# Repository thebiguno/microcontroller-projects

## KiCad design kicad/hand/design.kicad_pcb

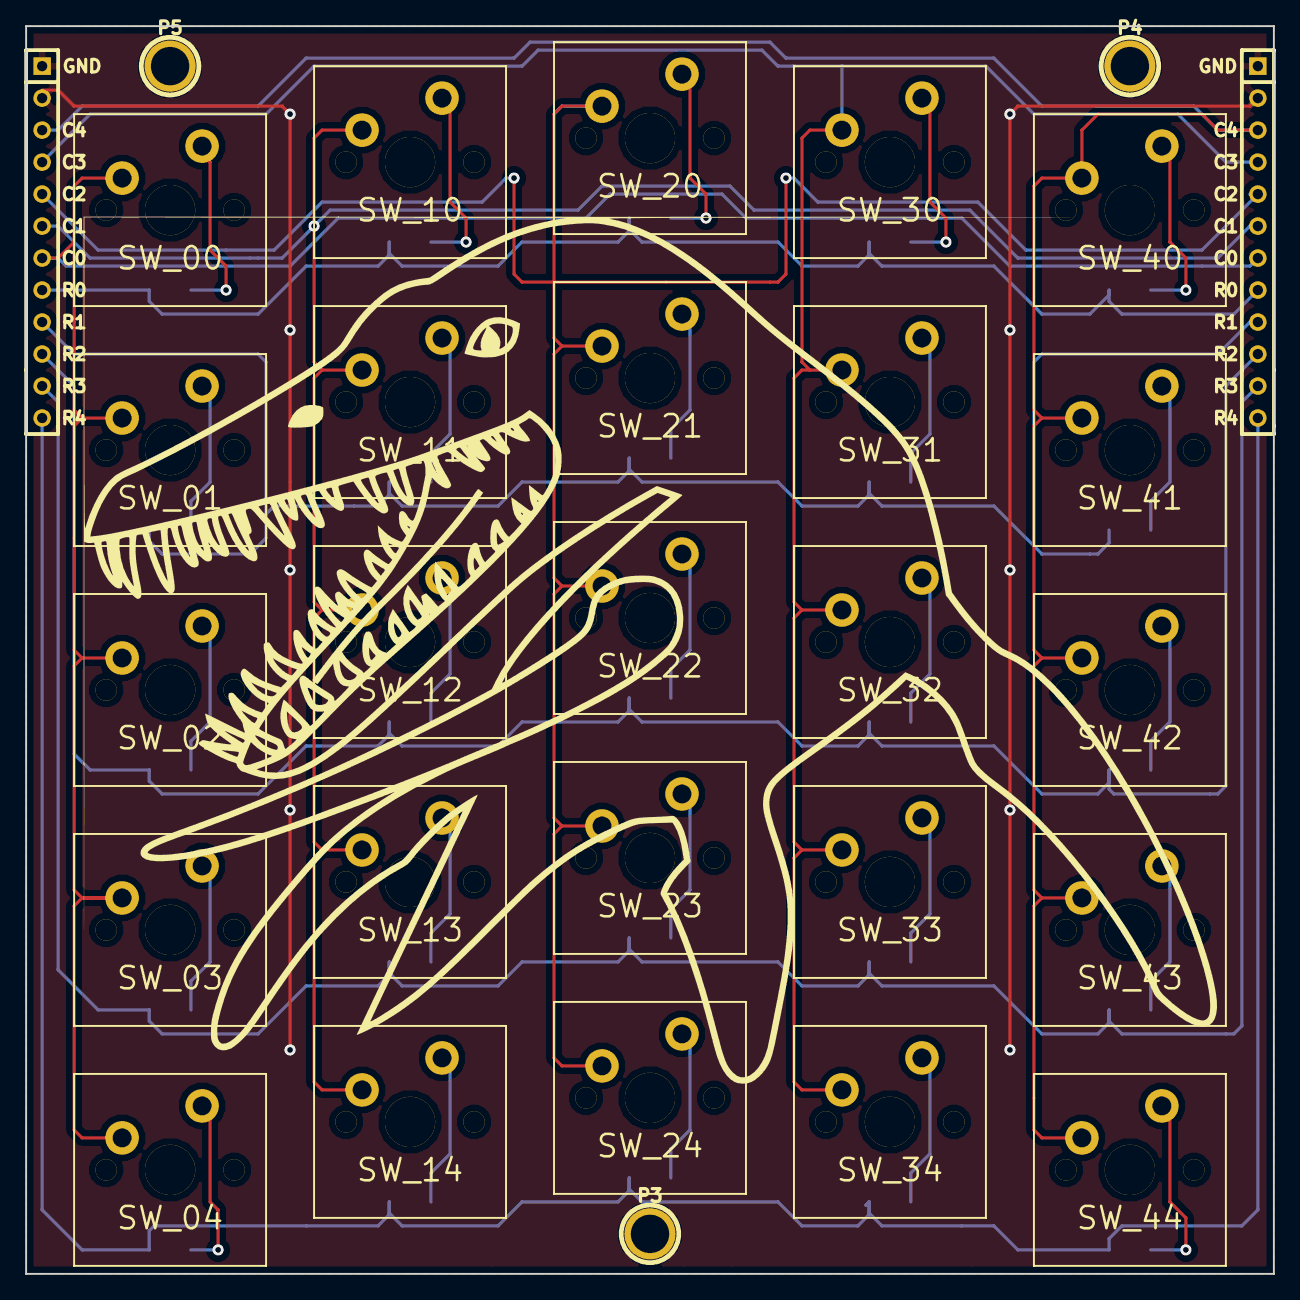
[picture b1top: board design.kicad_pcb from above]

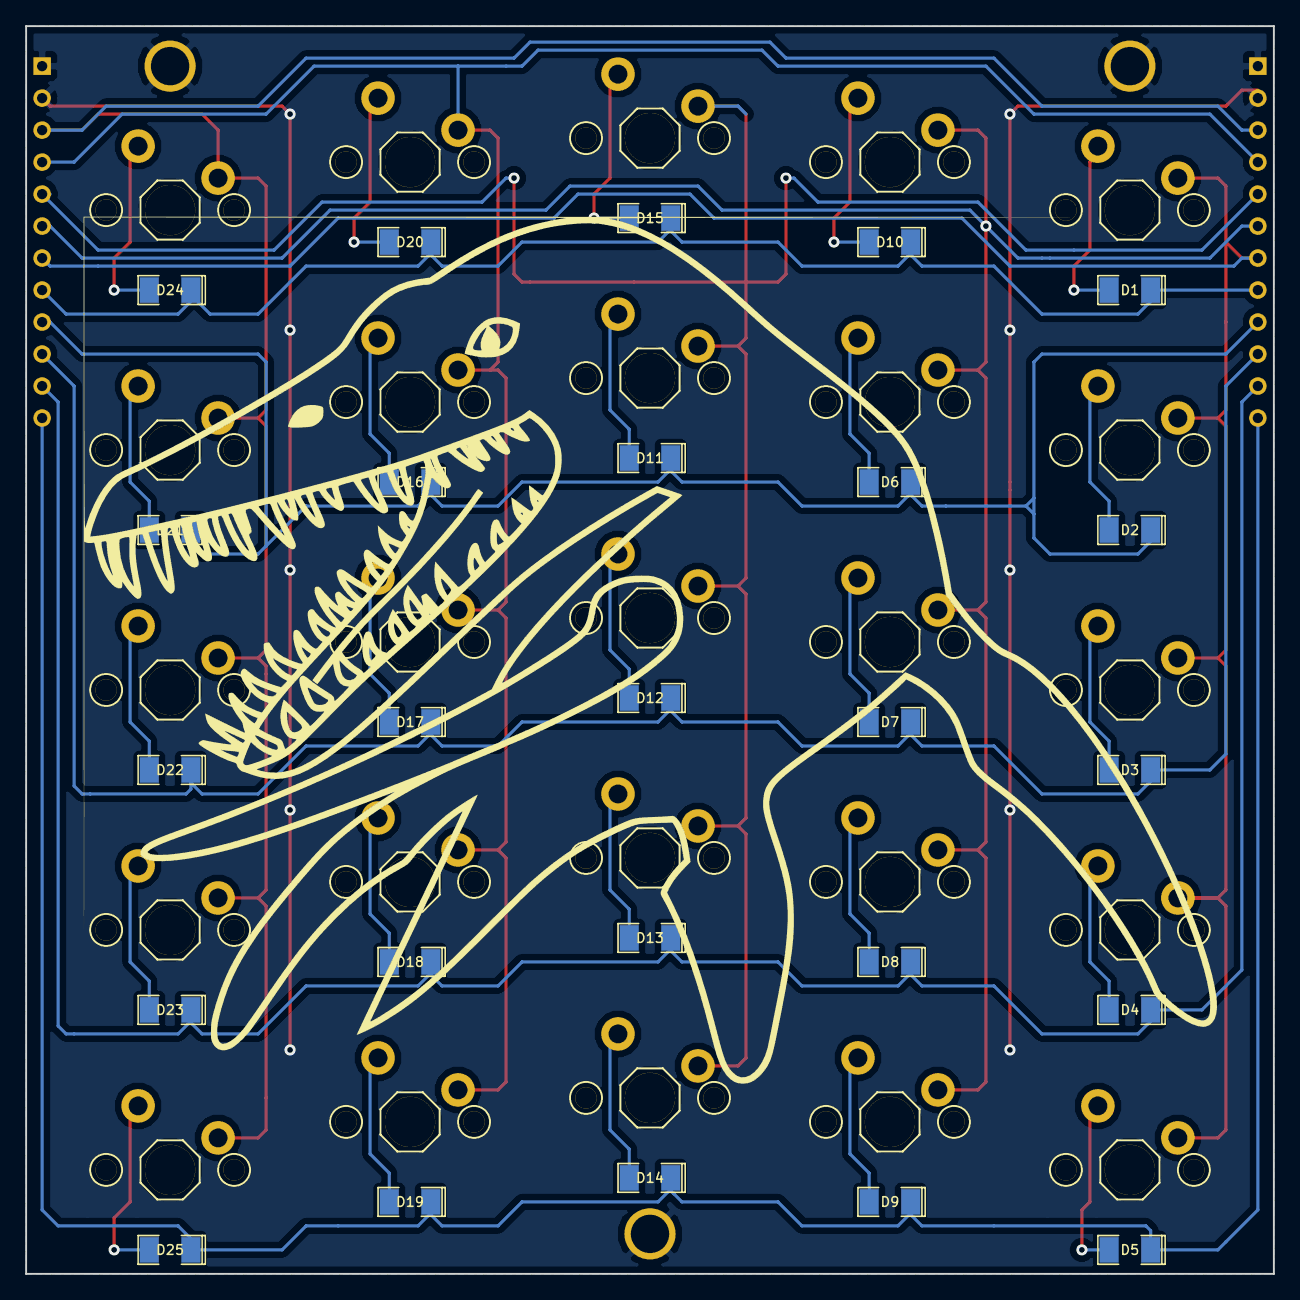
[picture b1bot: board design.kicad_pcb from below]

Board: 2 copper layers, 99.1 x 99.1 mm, 57 parts (25 on the bottom side), 36 nets.

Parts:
D1, D2, D3, D4, D5, D6, D7, D8, D9, D10, D11, D12, D13, D14, D15, D16, D17, D18, D19, D20, D21, D22, D23, D24, D25: DIODE; SM1206POL
P1, P2: CONN_12; SIL-12
P3, P4, P5: CONN_1; 1pin
SW1: SW_00; SW_PCB_2PIN
SW2: SW_01; SW_PCB_2PIN
SW3: SW_02; SW_PCB_2PIN
SW4: SW_03; SW_PCB_2PIN
SW5: SW_04; SW_PCB_2PIN
SW6: SW_11; SW_PCB_2PIN
SW7: SW_12; SW_PCB_2PIN
SW8: SW_13; SW_PCB_2PIN
SW9: SW_14; SW_PCB_2PIN
SW10: SW_10; SW_PCB_2PIN
SW11: SW_21; SW_PCB_2PIN
SW12: SW_22; SW_PCB_2PIN
SW13: SW_23; SW_PCB_2PIN
SW14: SW_24; SW_PCB_2PIN
SW15: SW_20; SW_PCB_2PIN
SW16: SW_31; SW_PCB_2PIN
SW17: SW_32; SW_PCB_2PIN
SW18: SW_33; SW_PCB_2PIN
SW19: SW_34; SW_PCB_2PIN
SW20: SW_30; SW_PCB_2PIN
SW21: SW_41; SW_PCB_2PIN
SW22: SW_42; SW_PCB_2PIN
SW23: SW_43; SW_PCB_2PIN
SW24: SW_40; SW_PCB_2PIN
SW25: SW_44; SW_PCB_2PIN
VAL: plesiosaurus_back
VAL#2: plesiosaurus_front

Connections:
C0: P1.7, P2.7, SW1.2, SW2.2, SW3.2, SW4.2, SW5.2
C1: P1.6, P2.6, SW6.2, SW7.2, SW8.2, SW9.2, SW10.2
C2: P1.5, P2.5, SW11.2, SW12.2, SW13.2, SW14.2, SW15.2
C3: P1.4, P2.4, SW16.2, SW17.2, SW18.2, SW19.2, SW20.2
C4: P1.3, P2.3, SW21.2, SW22.2, SW23.2, SW24.2, SW25.2
GND: P1.1, P1.2, P2.1, P2.2, P3.1, P4.1, P5.1
unnamed: D17.2, SW17.1
unnamed: D12.2, SW12.1
unnamed: D7.2, SW7.1
unnamed: D3.2, SW3.1
unnamed: D21.2, SW21.1
unnamed: D18.2, SW18.1
unnamed: D13.2, SW13.1
unnamed: D8.2, SW8.1
unnamed: D4.2, SW4.1
unnamed: D22.2, SW22.1
unnamed: D20.2, SW20.1
unnamed: D15.2, SW15.1
unnamed: D24.2, SW24.1
unnamed: D10.2, SW10.1
unnamed: D1.2, SW1.1
unnamed: D16.2, SW16.1
unnamed: D11.2, SW11.1
unnamed: D6.2, SW6.1
unnamed: D2.2, SW2.1
unnamed: D14.2, SW14.1
unnamed: D9.2, SW9.1
unnamed: D5.2, SW5.1
unnamed: D23.2, SW23.1
unnamed: D25.2, SW25.1
unnamed: D19.2, SW19.1
R0: D1.1, D10.1, D15.1, D20.1, D24.1, P1.8, P2.8
R1: D2.1, D6.1, D11.1, D16.1, D21.1, P1.9, P2.9
R2: D3.1, D7.1, D12.1, D17.1, D22.1, P1.10, P2.10
R3: D4.1, D8.1, D13.1, D18.1, D23.1, P1.11, P2.11
R4: D5.1, D9.1, D14.1, D19.1, D25.1, P1.12, P2.12

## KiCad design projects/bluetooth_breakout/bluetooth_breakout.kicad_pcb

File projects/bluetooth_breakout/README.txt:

How to program the HC-06 boards (which is apparently the one which I have, or some version like it) using this breakout board and a FTDI cable.

1) Physical connections
	a) Solder to the breakout board such that pin 1 on the module is closest to the 3v3 side, pin 13 is closest to GND, etc.  (Note that this is not the order of the actual pins; TX is pin 1, RX is pin 2, etc.  However we wanted this module to be in the same form factor as the XBee, thus 10 pins with VCC at one side and GND at the other, etc).  Truth be told, only pins 1, 2, 12, and 13 need to be soldered, but for stability it is best to just solder everything.
	b) Solder KEY pin to the pad on the back.  For my module, KEY is pin 34 (the one directly opposite VCC).  This can depend on the module in question... most HC-06 modules appear to have KEY as 26, while HC-05 modules appear to have key as 34.  I don't know if I just have a weird module with non-standard firmware or what, but for me KEY is 34 (even though other parts of the firmware appear to be closer to HC-06).  Yay for cheap eBay junk!
	c) Solder pins onto the 10 pin interface header and the 2 pin programming jumper.
2) Software
	a) Start by putting a jumper on the programming header.  This connects KEY to VCC, putting the module in programming mode.
	b) Connect RX / TX on the FTDI cable to the TX / RX on the board (using voltage dividers, zeners, whatever as needed to keep voltages at the proper level).
	c) In a serial terminal (Arduino's terminal works well), set to BAUD=9600 with no CR/LF.  (Note that other modules may require BAUD=38400 with LF+CR... again, this seems to be a HC-05 vs HC-06 thing, but my module appears to have properties of both of these).  (Also note that on my module, once you change the baud rate here, it also applies to programming it in the future.  My personal standard is to set these, plus other serial omodules like the XBee, to 38400.)
	d) Type "AT" (no quotes) to verify that the module is responding.  You should see "OK" echoed back.
	e) (For my use): Set Pin to 0000 and baud to 38400, if these are not already set properly.
	f) You can now use various AT commands to set baud rate, Bluetooth name, etc.  Google "HC-05 Programming" (or HC-06) for details.  See for instance http://www.puntoflotante.net/BOLT-SYSTEM-BLUETOOTH-AT-COMMANDS.htm for an example of what this will look like.

That's it!  Enjoy your Bluetooth serial hacking!

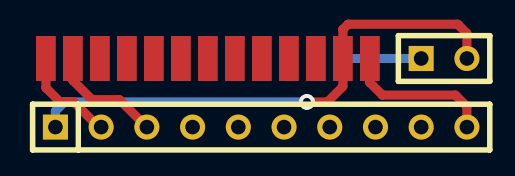
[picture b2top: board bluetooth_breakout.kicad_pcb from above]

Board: 2 copper layers, 6 parts (1 on the bottom side), 5 nets.

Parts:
P1: CONN_10; SIL-10
P2: CONN_13; SIL-13
P3: CONN_2; SIL-2
P4: CONN_1; 1PIN_SMD
VAL: REF; DIGITALCAVE_LOGO_SQUARE_SMALL_NO_TEXT_REVERSE
VAL#2: REF; DIGITALCAVE_URL_SMALL_REVERSE

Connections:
/GND: P1.10, P2.13
/RX: P1.3, P2.2
/TX: P1.2, P2.1
/VCC: P1.1, P2.12, P3.2
unnamed: P3.1, P4.1

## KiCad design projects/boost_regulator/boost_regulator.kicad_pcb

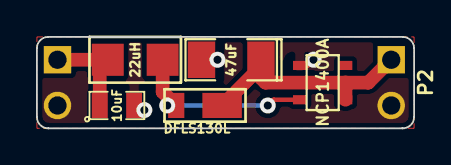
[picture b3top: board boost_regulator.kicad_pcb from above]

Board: 2 copper layers, 21.0 x 5.1 mm, 7 parts (0 on the bottom side), 4 nets.

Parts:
C1: 10uF; SM0805
C2: 47uF; SM1206POL
D1: DFLS130L; POWERDI_123
L1: 22uH; SM1007
P1, P2: CONN_2; PIN_ARRAY_2X1
VR1: NCP1400A; SOT23-5

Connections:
GND: C1.2, C2.2, P1.2, P2.2, VR1.4
unnamed: D1.1, L1.2, VR1.5
unnamed: C2.1, D1.2, P2.1, VR1.1, VR1.2
unnamed: C1.1, L1.1, P1.1

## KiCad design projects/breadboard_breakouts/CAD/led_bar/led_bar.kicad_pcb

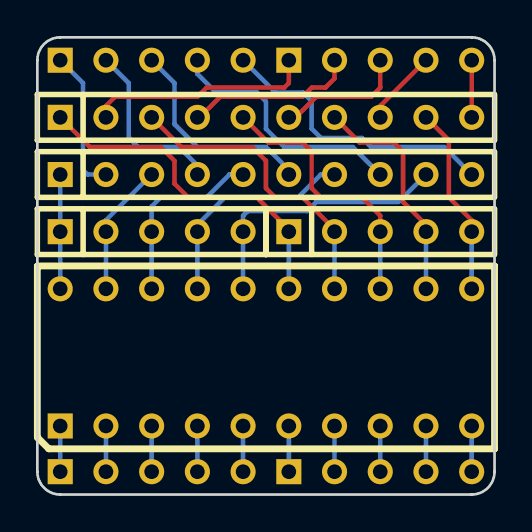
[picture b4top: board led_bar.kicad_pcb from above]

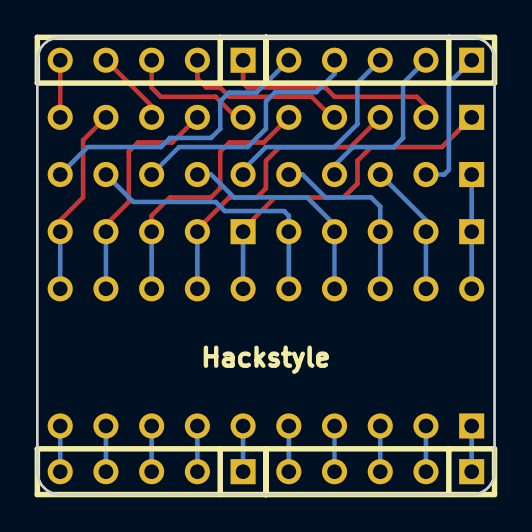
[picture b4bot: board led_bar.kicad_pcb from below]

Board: 2 copper layers, 25.4 x 25.4 mm, 9 parts (4 on the bottom side), 30 nets.

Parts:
BAR1: DOT-BAR2; 10LED_BAR
P1, P2, P3, P4, P5, P6: CONN_5; SIL-5
RP1, RP2: 220; SIL-10

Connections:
/11: BAR1.11, P4.5, RP2.9
/12: BAR1.12, P4.4, RP2.7
/13: BAR1.13, P4.3, RP2.5
/14: BAR1.14, P4.2, RP2.3
/15: BAR1.15, P4.1, RP2.1
/16: BAR1.16, P3.5, RP1.9
/17: BAR1.17, P3.4, RP1.7
/18: BAR1.18, P3.3, RP1.5
/19: BAR1.19, P3.2, RP1.3
/20: BAR1.20, P3.1, RP1.1
unnamed: BAR1.7, P2.2
unnamed: BAR1.8, P2.3
unnamed: BAR1.9, P2.4
unnamed: BAR1.10, P2.5
unnamed: P5.1, RP1.2
unnamed: P5.2, RP1.4
unnamed: P5.3, RP1.6
unnamed: P5.4, RP1.8
unnamed: P5.5, RP1.10
unnamed: P6.1, RP2.2
unnamed: P6.2, RP2.4
unnamed: BAR1.1, P1.1
unnamed: BAR1.2, P1.2
unnamed: BAR1.3, P1.3
unnamed: BAR1.4, P1.4
unnamed: BAR1.5, P1.5
unnamed: BAR1.6, P2.1
unnamed: P6.3, RP2.6
unnamed: P6.4, RP2.8
unnamed: P6.5, RP2.10

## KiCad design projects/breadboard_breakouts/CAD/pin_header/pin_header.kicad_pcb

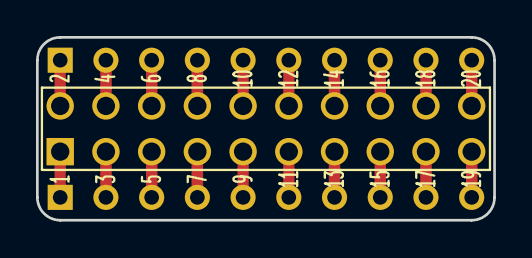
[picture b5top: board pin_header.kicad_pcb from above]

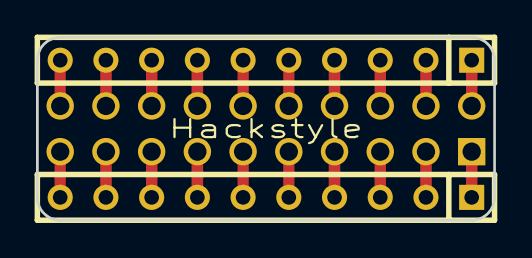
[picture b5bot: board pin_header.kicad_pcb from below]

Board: 2 copper layers, 25.4 x 10.2 mm, 3 parts (2 on the bottom side), 20 nets.

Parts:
J1, J2: SIL10; SIL-10
P1: CONN_10X2; PIN_ARRAY_10x2

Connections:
unnamed: J2.3, P1.6
unnamed: J2.2, P1.4
unnamed: J2.4, P1.8
unnamed: J2.5, P1.10
unnamed: J2.6, P1.12
unnamed: J2.7, P1.14
unnamed: J2.8, P1.16
unnamed: J2.9, P1.18
unnamed: J2.10, P1.20
unnamed: J2.1, P1.2
unnamed: J1.2, P1.3
unnamed: J1.3, P1.5
unnamed: J1.4, P1.7
unnamed: J1.5, P1.9
unnamed: J1.6, P1.11
unnamed: J1.7, P1.13
unnamed: J1.8, P1.15
unnamed: J1.9, P1.17
unnamed: J1.10, P1.19
unnamed: J1.1, P1.1

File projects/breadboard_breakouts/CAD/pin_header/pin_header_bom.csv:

ref,value,Item count
J1,J2,SIL10,2
P1,CONN_10X2,1

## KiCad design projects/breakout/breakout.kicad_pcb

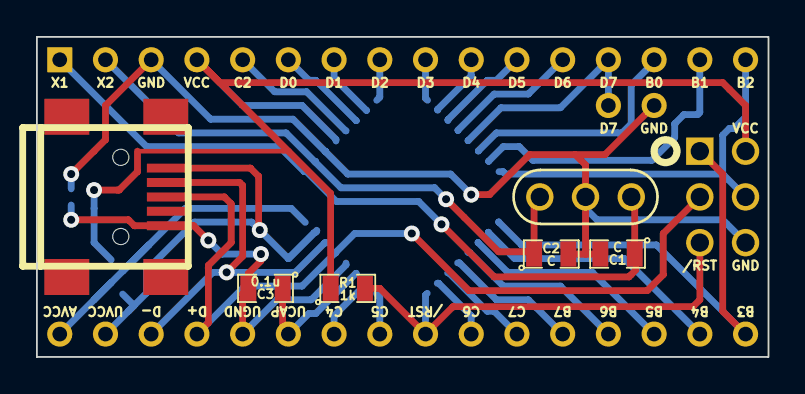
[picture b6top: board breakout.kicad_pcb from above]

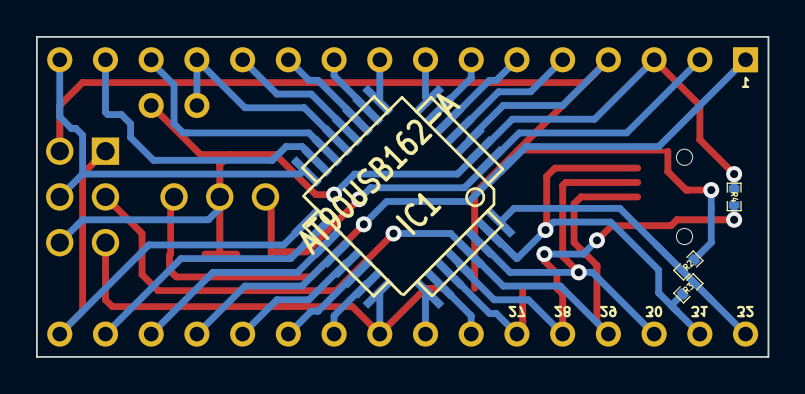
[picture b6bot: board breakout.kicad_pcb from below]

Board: 2 copper layers, 40.6 x 17.8 mm, 16 parts (4 on the bottom side), 32 nets.

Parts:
C1, C2: C; SM0805
C3: 0.1u; SM0805
CON1: USB-MINI-B; USB_MINI_B_fixed
IC1: AT90USB162-A; TQFP32
P1: CONN_2; SIL-2
P2, P3, P4, P5: CONN_8; SIL-8
P7: ISP
R1: 1k; SM0805
R2, R3, R4: 0; SM0402_r
X1: CRYSTAL_RESONATOR

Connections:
/a1: C1.1, IC1.1, P2.1, X1.1
/a2: C2.1, IC1.2, P2.2, X1.2
/a4: IC1.4, P2.4, P7.2, R1.1, R2.1
/a5: IC1.5, P2.5
/a6: IC1.6, P2.6
/a7: IC1.7, P2.7
/a8: IC1.8, P2.8
/a9: IC1.9, P3.1
/a10: IC1.10, P3.2
/a11: IC1.11, P3.3
/a12: IC1.12, P3.4
/a13: IC1.13, P1.1, P3.5
/a14: IC1.14, P3.6
/a15: IC1.15, P3.7
/a16: IC1.16, P3.8, P7.4
/a17: IC1.17, P4.1, P7.1
/a18: IC1.18, P4.2
/a19: IC1.19, P4.3
/a20: IC1.20, P4.4
/a21: IC1.21, P4.5
/a22: IC1.22, P4.6
/a23: IC1.23, P4.7
/a24: IC1.24, P4.8, P7.5, R1.2
/a25: IC1.25, P5.1
/a26: IC1.26, P5.2
/a27: C3.1, IC1.27, P5.3
/a28: C3.2, CON1.5, IC1.28, P5.4, R4.2
/a29: CON1.3, IC1.29, P5.5, P7.3
/a30: CON1.2, IC1.30, P5.6
/a31: CON1.1, IC1.31, P5.7, R3.1
/a32: IC1.32, P5.8, R2.2, R3.2
GND: C1.2, C2.2, IC1.3, P1.2, P2.3, P7.6, R4.1, X1.3
